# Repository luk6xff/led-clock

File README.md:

# led-clock
LED clock with some fancy features.

## Details
The clock is configurable over web inteface. The time is provided by extremaly accurate RTC DS3231. It can be also synchronized with NTP server.
It receives and display meteo data from external LORA sensor.
You can also configure [openweather map API](https://openweathermap.org/) to get and display latest weather forecast for your city.
The clock UI supports two languages currently: polish and english.
You can check below the videos to see how it works in action:

* 
* 

## Some pics
### Device
* Printed Case:

* LoRa meteo sensor:

* Custom Case:

* Prototype:

### Web app

### Schematics
* Clock:

* LoRa external sensor:

## Parts used
All the modules used in the project are listed [here](./docs/BOM.md).

## The project contains of 2 subprojects:

### [esp32-app](./esp32-app/README.md)
Main clock application based on esp32 wroom device. README here: [esp32-app-readme](./esp32-app/README.md)

### [sensor-app](./sensor-app/README.md)
Sensor board application based on STM32L031F6Px. README here: [sensor-app-readme](./sensor-app/README.md)

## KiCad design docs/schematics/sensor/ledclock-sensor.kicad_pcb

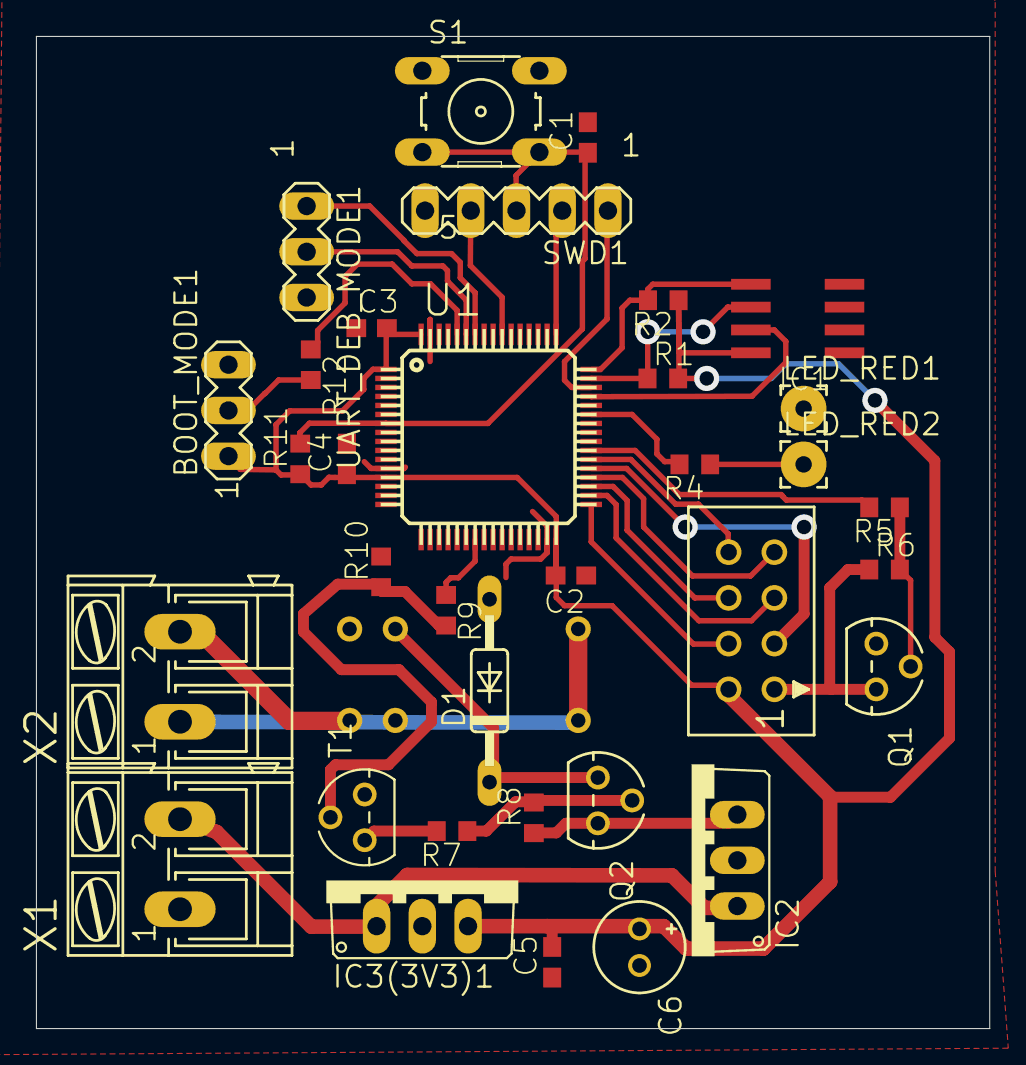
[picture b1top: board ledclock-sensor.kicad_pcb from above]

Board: 2 copper layers, 53.0 x 55.1 mm, 35 parts (0 on the bottom side), 33 nets.

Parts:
BOOT_MODE1: MA03-1
C1, C2, C3, C5: 100nF; C0603
C4: 10nF; C0603
C6: CPOL-EUE2-5; E2-5
CON1: CON10
D1: 1N4148DO35-10; DO35-10
IC1: 24SN; SO-08
IC2, IC3(3V3)1: 78TV; TO220V
LED_RED1, LED_RED2: 2,54_0,9
Q1, Q2: BC557; TO92
R1, R2, R4: 4.7k; R0603
R5, R7, R9: 5.1k; R0603
R6, R8, R10: 10k; R0603
R11, R12: 100k; R0603
S1: 10-XX; B3F-10XX
SWD1: MA05-1
T1: BC547; TO92
U1: STM32F10XRXT6; TQFP64
U$1: PRZEKAZ; FPR
UART_DEB_MODE1: MA03-1
X1, X2: AK300_2

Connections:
+5V: IC2.3, Q2.1, R8.1
+24V: IC2.1, IC3(3V3)1.1, X1.2
/CE: CON1.3, U1.37
/IRQ: CON1.8, U1.38
/MISO: CON1.7, U1.36
/NRST: C1.1, R11.2, S1.3, S1.4, SWD1.3, U1.7
/RX: U1.59, UART_DEB_MODE1.2
/SCK: CON1.5, U1.34
/SWCLK: SWD1.2, U1.49
/SWDIO: SWD1.1, U1.46
/SWO: SWD1.4, U1.55
/TX: U1.58, UART_DEB_MODE1.1
GND: BOOT_MODE1.3, C1.2, C2.1, C3.1, C4.2, C5.1, C6.-, D1.A, IC1.1, IC1.2, IC1.3, IC1.4, IC2.2, IC3(3V3)1.2, LED_RED1.1, Q1.3, R10.2, S1.1, S1.2, SWD1.5, T1.1, U1.12, U1.31, U1.63, U$1.P$4, UART_DEB_MODE1.3, X1.1
unnamed: BOOT_MODE1.2, R12.2
unnamed: CON1.1, Q1.1, R6.1
unnamed: CON1.4, U1.33
unnamed: CON1.6, U1.35
unnamed: D1.C, Q2.3, U$1.P$3
unnamed: IC1.5, R2.2, U1.48
unnamed: IC1.6, R1.1, U1.47
unnamed: IC1.7, U1.45
unnamed: LED_RED2.1, R4.1
unnamed: Q1.2, R5.1, R6.2
unnamed: Q2.2, R7.1, R8.2
unnamed: R4.2, U1.43
unnamed: R5.2, U1.39
unnamed: R7.2, T1.3
unnamed: R9.1, U1.23
unnamed: R9.2, R10.1, T1.2
unnamed: R12.1, U1.60
unnamed: U$1.P$1, U$1.P$2, X2.1
unnamed: U$1.P$6, X2.2
VCC: BOOT_MODE1.1, C2.2, C3.2, C4.1, C5.2, C6.+, CON1.2, IC1.8, IC3(3V3)1.3, R1.2, R2.1, R11.1, U1.1, U1.13, U1.32, U1.64

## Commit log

2020-07-07 BOM first draft
2020-07-07 esp32 skeleton
2020-07-07 esp32 dev link
2020-07-24 Project structure rework
2020-07-25 demo rtos task
2020-07-29 MAX72xx driver lib tests
2020-07-30 MD_LIBRARY more tests done
2020-08-04 Display demo done
2020-08-06 Display module created
2020-08-06 Not used LEDMatrixLibrary Removed
2020-08-06 light sensor
2020-08-06 Auto brightness feature done
2020-08-07 SX1278 library skeleton added
2020-08-07 datasheets update
2020-08-09 sx1278 library modified
2020-08-09 sx1278 docs
2020-08-11 sensor app created, LORA communication done
2020-08-11 bmp180 first draft
2020-08-14 bmp180 draft
2020-08-18 bmp180 demo
2020-08-18 bmp180 done
2020-08-19 BME280 first draft
2020-08-30 bme280 finished
2020-08-30 remove bmp180
2020-08-31 msg frame design
2020-08-31 recv msg from sensor board done
2020-08-31 Fix for checksum
2020-08-31 Msg error handling
2020-08-31 standby mode - first draft
2020-09-01 App skeleton
2020-09-03 max44009 library draft
2020-09-03 light and rtc tests
2020-10-05 Back to work
2020-10-08 Font for zones
2020-10-09 Stable clcok display
2020-10-09 Stable clock display
2020-10-12 polish font update
2020-10-16 DisplayTask created
2020-10-16 Display Task sync
2020-10-16 Display Task Task stack increased
2020-10-17 First rtos working demo
2020-10-18 NtpClient
2020-10-18 Wifi connection task
2020-10-18 ntp sync queue added
2020-10-18 Wire sync issue - fix
2020-10-19 Disable light sensor - issue to be fixed
2020-10-19 Task cleanup
2020-10-23 Owm api and task done
2020-10-24 SX1278 library enabled on STM
2020-10-24 Sensor app rework
2020-10-25 Stop mode on sensor done
2020-10-25 Stop mode on STM32 done
2020-10-25 Stop mode on sensor - works
2020-10-25 RTC backup domain registers - finished
2020-10-25 RadioTask - create pt1
2020-10-25 RadioTask - works
2020-10-25 Radio Sensor task done
2020-10-25 Sensor task queue added
2020-10-25 Time queue decrease send period
2020-10-26 Sensor app - WWDG enabled
2020-10-26 Sensor app - LPUART1
2020-10-26 Sensor app - ADC VBATT draft
2020-10-27 Wifi captive portal done
2020-11-02 Web server demo
2020-11-03 AsyncWebServer demo
2020-11-11 WebServer - pt1
2020-11-11 webserver pt2
2020-11-12 WebServer - First OTA version done
2020-11-13 Webserver js stuff
2020-11-14 Save cfg webserver part
2020-11-15 Setting to/from json concept
2020-11-15 Cfg - pt2
2020-11-16 Cfg - pt3
2020-11-16 Cfg - pt4
2020-11-16 Cfg - skip store if no change
2020-11-16 Cfg - pt5
2020-11-17 Fix for own data format
2020-11-17 Alert boxes added
2020-11-17 App tab added
2020-11-17 Cfg save validation added
2020-11-17 Global display msg buffer created
2020-11-18 Captive portal based on async server done
2020-11-18 Fix logo layout issue
2020-11-18 Set dt fix
2020-11-18 Update DT set/get
2020-11-18 i18n
2020-11-19 Wifi reconnect mechanism
2020-11-19 Fix for servers reinint during reconnection
2020-11-19 Radio task and message added
2020-11-19 Vbat msg change
2020-11-19 Show/hide passwords added
2020-11-19 Fonts cleanup
2020-11-20 App settings, more fixes
2020-11-20 Light sensor fixed and enabled
2020-11-20 App vars created and updated on post build script
2020-11-21 Lora settings improved
2020-11-23 Lora bare metal library added
2020-11-23 Differences in test lora regs
2020-11-23 LORA libe test app finished
2020-11-23 Lora lib more fixes
2020-11-24 lora on sensor board working
2020-11-24 Lora Ping pong app done
2020-11-24 Bare metal lora driver finished
2020-11-25 Radio health check status task added
2020-11-27 LedClock version 0.1.0 done
2020-12-05 radio-sensor schematic done
2020-12-05 Temp display resolution fixed to 1 decimal
2020-12-06 Readme update
2020-12-21 Fix for humidity readout in BME280 lib
2020-12-29 Global queue for input display msgs done
2021-01-15 Lora sensor app port to my Lora library
2021-01-16 Repeat last received Radio message seetings added
2021-01-16 Change AP server IP
2021-01-16 Fix for repeating last radio messages
2021-01-17 LoraTest app update
2021-02-28 Config Mgr-init
2021-02-28 Cfg manager update
2021-03-01 unitests uploaded
2021-03-03 Settings update
2021-03-21 Internal environment data readout
2021-07-08 Internal temperature readout defaults
2021-07-08 Fix for print time not a msg range
2021-07-08 AutoDisplayIntensity disabled by default
2021-07-09 Int env data added to UI
2021-07-13 LedClock case final version
2021-07-14 Case stl files update
2021-07-15 App global status implementation
2021-07-15 LedClock Version 0.0.1 released
2021-07-16 OTA update display handling
2021-07-16 Day info runner
2021-07-16 pictures update
2021-07-16 BOM update
2021-07-16 EXT sensor status modified
2021-07-16 ota cleanup
2021-07-20 RTC change zone method done - but not used yet
2021-07-21 sensor-app README update
2021-07-21 sensor app solution cleanup
2021-07-23 Display clear method fix
2021-08-05 Release v1.1
2022-10-03 Update build scripts
2022-10-04 BME280 library, wifi manager pt1
2022-10-05 web_config_param draft
2022-10-05 web_config_param draft2
2022-10-06 update config
2022-11-20 TimeConfig added
2022-12-22 Config update
2022-12-22 Cleanup pt1
2022-12-22 Cleanup pt2
2022-12-24 Update to V1
2022-12-24 V1 Zosia gift
2022-12-24 V1 done
